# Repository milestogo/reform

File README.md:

#MNT keyboard remix
See keyboard-pcb for remix

# MNT Reform

This is the main repository for the MNT Reform open source laptop.

For details, check out [Finishing Reform](https://mntre.com/media/reform_md/2020-01-18-finishing-reform.html) and related articles.

## Impressions

## License

Copyright 2018-2020 MNT Research GmbH.

The following licenses are used in the project, unless specified differently in a particular subfolder:

- Schematics, PCBs: [CERN-OHL-S v2](https://www.ohwr.org/project/cernohl/wikis/uploads/002d0b7d5066e6b3829168730237bddb/cern_ohl_s_v2.txt)
- Other documentation, artwork, photos and drawings that are not trademarks (see below): [CC-BY-SA 4.0](https://creativecommons.org/licenses/by-sa/4.0/legalcode)
- Software, firmware: Various. [GPL 3.0](https://www.gnu.org/licenses/gpl-3.0.en.html) if not specified otherwise in the file/subdirectory.

The "MNT" and "MNT REFORM" logos are trademarks of MNT Research GmbH. You may not use these in derived works. The reason for this is that we cannot be responsible for regulatory issues with derived boards and we cannot support them. If someone sees an MNT brand on a product, it has to be clear that it comes from MNT Research and not from a third party.

## Made With

* [KiCAD EDA](http://kicad-pcb.org/)
* [OpenSCAD](https://www.openscad.org/)
* [LUFA](http://www.fourwalledcubicle.com/LUFA.php)
* Autodesk Fusion (Case parts)

## MNT Reform Team

* **Lukas F. Hartmann (mntmn)** - *Schematics, PCB*
* **Ana Dantas** - *Industrial Design*
* **Greta Melnik** - *Quality & Assembly, Sleeve*

## Credits and Contributions

* [fully automated technologies](https://fully.automated.ee/) - *inrush limiter circuit*

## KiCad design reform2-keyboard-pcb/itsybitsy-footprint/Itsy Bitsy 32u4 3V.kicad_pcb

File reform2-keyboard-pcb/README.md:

# keyboard remix by milestogo

This keyboard design is for educational purposes: for me to learn through experimenting, or for for you to educate me. 
Little remains of MNT's tested design. I have not tested. It may have dangerous or time-wasting errors. 

Changes from MNT reform
- Ergonomic key layout. 
- Removed backlight
- Added partial RGB backlighting. Keys ESC,~,1,2, F, Thumb keys, J, 9,0,-,= have backlights. This is enough to show battery voltage or where to put your hand in the dark. There are jumpers to bypass the top row LEDs, or add separate LED strips. This uses SK Mini-E rgb lights. Since they are bottom mount and optional, the power caps for them are also bottom & optional. 
- Added optional Kailh sockets for switches without RGB backlight. These sockets are cheaper than switches, so I like them in protototypes. there probably isn't thermal or short circuit clearance above the MNT motherboard, so use the direct direct solder holes.
- Removed surface mount Atmega32u4 and related voltage chips (cost and chip shortages). Instead it uses the 3 volt Adafruit itsy bitsy. https://learn.adafruit.com/introducting-itsy-bitsy-32u4/pinouts
you must hack a USB cable to connect the MCU  to the keyboard (see screenprint for "airwire"). 
- Optional power off switch/jumper that can completly remove power to the keyboard.
- Lots of break out pins, so that it should be possible to use the PCB with other MCUs.  
- Desktop option for through hole OLED modules. Available from online retailers

These changes are made available under the MIT License: 
Copyright © 2022 milestogo

Permission is hereby granted, free of charge, to any person obtaining a copy of this software and associated documentation files (the “Software”), to deal in the Software without restriction, including without limitation the rights to use, copy, modify, merge, publish, distribute, sublicense, and/or sell copies of the Software, and to permit persons to whom the Software is furnished to do so, subject to the following conditions:

The above copyright notice and this permission notice shall be included in all copies or substantial portions of the Software.

THE SOFTWARE IS PROVIDED “AS IS”, WITHOUT WARRANTY OF ANY KIND, EXPRESS OR IMPLIED, INCLUDING BUT NOT LIMITED TO THE WARRANTIES OF MERCHANTABILITY, FITNESS FOR A PARTICULAR PURPOSE AND NONINFRINGEMENT. IN NO EVENT SHALL THE AUTHORS OR COPYRIGHT HOLDERS BE LIABLE FOR ANY CLAIM, DAMAGES OR OTHER LIABILITY, WHETHER IN AN ACTION OF CONTRACT, TORT OR OTHERWISE, ARISING FROM, OUT OF OR IN CONNECTION WITH THE SOFTWARE OR THE USE OR OTHER DEALINGS IN THE SOFTWARE.

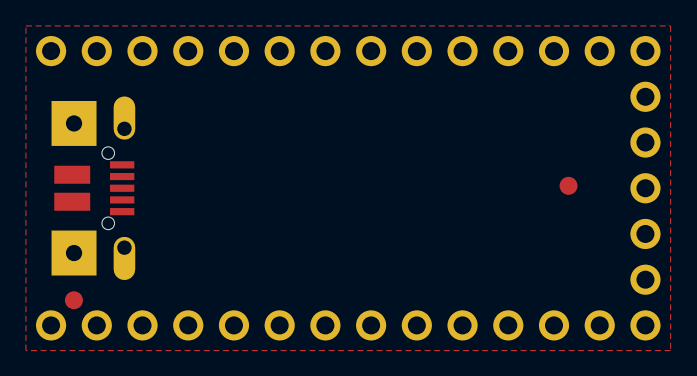
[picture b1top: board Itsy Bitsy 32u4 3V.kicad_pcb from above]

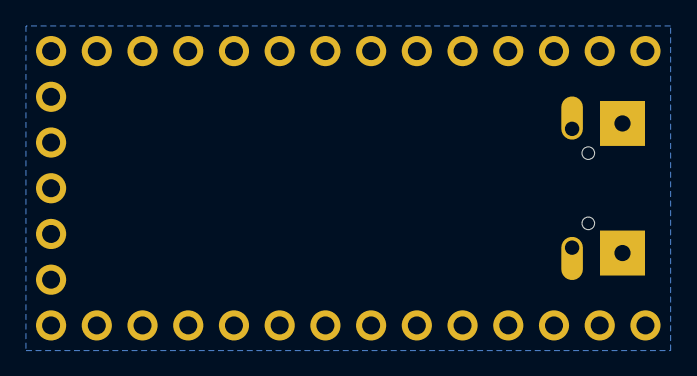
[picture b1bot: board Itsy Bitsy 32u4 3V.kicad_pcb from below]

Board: 2 copper layers, 9 parts (2 on the bottom side), 2 nets, no tracks yet.

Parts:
JP1: 1X05_ROUND
JP2, JP4: 1X14_ROUND70
U$2: PCBFEAT-REV-040
U$4: ADAFRUIT_5MM
U$7: ADAFRUIT_3.5MM
U$34, U$35: FIDUCIAL""; FIDUCIAL_1MM
X3: microUSB; 4UCONN_20329_V2

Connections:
GND: JP1.4, JP2.2, JP4.1, X3.BASE@1, X3.BASE@2, X3.GND, X3.SPRT@1, X3.SPRT@2, X3.SPRT@3, X3.SPRT@4
VBUS: JP2.3, X3.VBUS

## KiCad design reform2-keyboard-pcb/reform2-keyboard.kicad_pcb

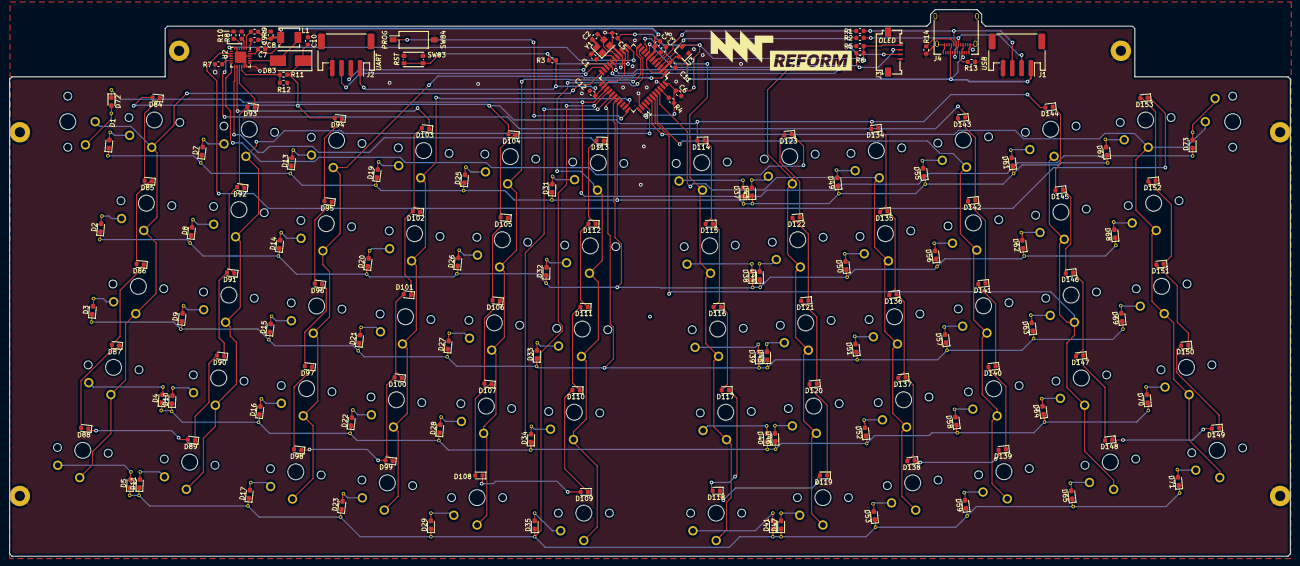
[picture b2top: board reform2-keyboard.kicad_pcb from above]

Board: 2 copper layers, 275.9 x 117.8 mm, 230 parts (1 on the bottom side), 168 nets.

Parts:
C1, C2: 18pF; C_0603_1608Metric
C3, C5, C8, C9, C11, C12: 1uF; C_0603_1608Metric
C4, C6: 0.1uF; C_0603_1608Metric
C7, C10: 4.7uF; C_0603_1608Metric
D1, D2, D3, D4, D5, D7, D8, D9, D10, D11, D13, D14, D15, D16, D17, D19, D20, D21, D22, D23, D25, D26, D27, D28, D29, D31, D32, D33, D34, D35, D37, D38, D39, D40, D41, D43, D44, D45, D46, D47, D49, D50, D51, D52, D53, D55, D56, D57, D58, D59, D61, D62, D63, D64, D65, D67, D68, D69, D70, D71, D72, D73: MMDL914T1G; D_0603_1608Metric_Pad1.05x0.95mm_HandSolderPlusVias
D83: B250-13-F; D_SMB_Handsoldering
D84, D85, D86, D87, D88, D89, D90, D91, D92, D93, D94, D95, D96, D97, D98, D99, D100, D101, D102, D103, D104, D105, D106, D107, D108, D109, D110, D111, D112, D113, D114, D115, D116, D117, D118, D119, D120, D121, D122, D123, D134, D135, D136, D137, D138, D139, D140, D141, D142, D143, D144, D145, D146, D147, D148, D149, D150, D151, D152, D153: WLED; LED_0603_1608Metric
GFX1, GFX2: MNT; mntreform
H1: MH1; MountingHole_2.2mm_M2_Pad
H2: MH2; MountingHole_2.2mm_M2_Pad
H3: MH3; MountingHole_2.2mm_M2_Pad
H4: MH4; MountingHole_2.2mm_M2_Pad
H5: MH5; MountingHole_2.2mm_M2_Pad
H6: MH6; MountingHole_2.2mm_M2_Pad
J1: USB; JST_PH_S4B-PH-SM4-TB_1x04-1MP_P2.00mm_Horizontal
J2: UART; JST_PH_S4B-PH-SM4-TB_1x04-1MP_P2.00mm_Horizontal
J3: AUX; Molex_200528-0040_1x04-1MP_P1.00mm_Horizontal
J4: USB_C_Receptacle_USB2.0; USB_C_Receptacle_Amphenol_12401610E4-2A
L1: 10uH; IND_SRP4020TA-150M
R1, R2: 22; R_0603_1608Metric
R3: 10k; R_0603_1608Metric
R4, R9: 0; R_0603_1608Metric
R5, R6: 4.7k; R_0603_1608Metric
R7: 62K; R_0603_1608Metric
R8: 604K; R_0603_1608Metric
R10: 715K; R_0603_1608Metric
R11: 1M; R_0603_1608Metric
R12: 54.9K; R_0603_1608Metric
R13, R14: 5.1k; R_0603_1608Metric
SW1, SW2, SW3, SW4, SW5, SW7, SW8, SW9, SW10, SW11, SW13, SW14, SW15, SW16, SW17, SW19, SW20, SW21, SW22, SW23, SW25, SW26, SW27, SW28, SW29, SW31, SW32, SW33, SW34, SW35, SW37, SW38, SW39, SW40, SW41, SW43, SW44, SW45, SW46, SW47, SW49, SW50, SW51, SW52, SW53, SW55, SW56, SW57, SW58, SW59, SW61, SW62, SW63, SW64, SW65, SW67, SW68, SW69, SW70, SW71, SW72, SW73: Choc; PG1350
SW83: RESET; SW_Push_1P1T_NO_CK_KMR2
SW84: SW_DIP_x01; SW_DIP_SPSTx01_Slide_Omron_A6S-110x_W8.9mm_P2.54mm
U1: ATMEGA32U4-AU; TQFP-44_10x10mm_Pitch0.8mm
U2: TPS61185; VQFN-24-1EP_4x4mm_P0.5mm_EP2.45x2.45mm
U3: MCP1700-3302E_SOT23; SOT-23
Y1: 16MHz; Crystal_SMD_3225-4Pin_3.2x2.5mm

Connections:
+3V3: C5.1, C6.1, C12.1, J2.1, J3.1, R3.1, R4.2, R5.1, R6.1, U1.14, U1.24, U1.34, U1.44, U3.2
+5V: C4.1, C7.1, C8.1, C11.1, J1.1, J4.A4, J4.A9, J4.B4, J4.B9, L1.1, R9.1, U1.2, U1.7, U2.23, U3.3
/Reform KBD MCU/UD+: R1.1, U1.4
/Reform KBD MCU/UD-: R2.1, U1.3
COL1: SW1.1, SW2.1, SW3.1, SW4.1, SW5.1, SW72.1, U1.22
COL2: SW7.1, SW8.1, SW9.1, SW10.1, SW11.1, U1.36
COL3: SW13.1, SW14.1, SW15.1, SW16.1, SW17.1, U1.1
COL4: SW19.1, SW20.1, SW21.1, SW22.1, SW23.1, U1.32
COL5: SW25.1, SW26.1, SW27.1, SW28.1, SW29.1, U1.11
COL6: SW31.1, SW32.1, SW33.1, SW34.1, SW35.1, U1.10
COL7: SW37.1, SW38.1, SW39.1, SW40.1, SW41.1, U1.9
COL8: SW43.1, SW44.1, SW45.1, SW46.1, SW47.1, U1.8
COL9: SW49.1, SW50.1, SW51.1, SW52.1, SW53.1, U1.41
COL10: SW55.1, SW56.1, SW57.1, SW58.1, SW59.1, U1.40
COL11: SW61.1, SW62.1, SW63.1, SW64.1, SW65.1, U1.39
COL12: SW67.1, SW68.1, SW69.1, SW70.1, SW71.1, SW73.1, U1.38
D+: J1.3, J4.A6, J4.B6, R1.2
D-: J1.2, J4.A7, J4.B7, R2.2
DISP_SCL: J3.2, R6.2, U1.18
DISP_SDA: J3.3, R5.2, U1.19
GND: C1.2, C2.2, C3.2, C4.2, C5.2, C6.2, C7.2, C8.2, C9.2, C10.2, C11.2, C12.2, H1.1, H2.1, H3.1, H4.1, H5.1, H6.1, J1.4, J2.4, J3.4, J4.A1, J4.A12, J4.B1, J4.B12, J4.S1, R7.2, R8.2, R10.2, R12.2, R13.1, R14.2, SW83.2, SW84.2, U1.5, U1.15, U1.23, U1.35, U1.43, U2.5, U2.17, U2.18, U2.22, U2.25, U3.1, Y1.2, Y1.4
unnamed: C1.1, U1.17, Y1.1
unnamed: C2.1, U1.16, Y1.3
unnamed: C3.1, U1.6
unnamed: C9.1, U2.24
unnamed: C10.1, D83.1, D84.2, D94.2, D104.2, D114.2, D134.2, D144.2, R11.1
unnamed: D1.2, SW1.2
unnamed: D2.2, SW2.2
unnamed: D3.2, SW3.2
unnamed: D4.2, SW4.2
unnamed: D5.2, SW5.2
unnamed: D7.2, SW7.2
unnamed: D8.2, SW8.2
unnamed: D9.2, SW9.2
unnamed: D10.2, SW10.2
unnamed: D11.2, SW11.2
unnamed: D13.2, SW13.2
unnamed: D14.2, SW14.2
unnamed: D15.2, SW15.2
unnamed: D16.2, SW16.2
unnamed: D17.2, SW17.2
unnamed: D19.2, SW19.2
unnamed: D20.2, SW20.2
unnamed: D21.2, SW21.2
unnamed: D22.2, SW22.2
unnamed: D23.2, SW23.2
unnamed: D25.2, SW25.2
unnamed: D26.2, SW26.2
unnamed: D27.2, SW27.2
unnamed: D28.2, SW28.2
unnamed: D29.2, SW29.2
unnamed: D31.2, SW31.2
unnamed: D32.2, SW32.2
unnamed: D33.2, SW33.2
unnamed: D34.2, SW34.2
unnamed: D35.2, SW35.2
unnamed: D37.2, SW37.2
unnamed: D38.2, SW38.2
unnamed: D39.2, SW39.2
unnamed: D40.2, SW40.2
unnamed: D41.2, SW41.2
unnamed: D43.2, SW43.2
unnamed: D44.2, SW44.2
unnamed: D45.2, SW45.2
unnamed: D46.2, SW46.2
unnamed: D47.2, SW47.2
unnamed: D49.2, SW49.2
unnamed: D50.2, SW50.2
unnamed: D51.2, SW51.2
unnamed: D52.2, SW52.2
unnamed: D53.2, SW53.2
unnamed: D55.2, SW55.2
unnamed: D56.2, SW56.2
unnamed: D57.2, SW57.2
unnamed: D58.2, SW58.2
unnamed: D59.2, SW59.2
unnamed: D61.2, SW61.2
unnamed: D62.2, SW62.2
unnamed: D63.2, SW63.2
unnamed: D64.2, SW64.2
unnamed: D65.2, SW65.2
unnamed: D67.2, SW67.2
unnamed: D68.2, SW68.2
unnamed: D69.2, SW69.2
unnamed: D70.2, SW70.2
unnamed: D71.2, SW71.2
unnamed: D72.2, SW72.2
unnamed: D73.2, SW73.2
unnamed: D83.2, L1.2, U2.19, U2.20
unnamed: D84.1, D85.2
unnamed: D85.1, D86.2
unnamed: D86.1, D87.2
unnamed: D87.1, D88.2
unnamed: D88.1, D89.2
unnamed: D89.1, D90.2
unnamed: D90.1, D91.2
unnamed: D91.1, D92.2
unnamed: D92.1, D93.2
unnamed: D93.1, U2.15
unnamed: D94.1, D95.2
unnamed: D95.1, D96.2
unnamed: D96.1, D97.2
unnamed: D97.1, D98.2
unnamed: D98.1, D99.2
unnamed: D100.1, D101.2
unnamed: D99.1, D100.2
unnamed: D101.1, D102.2
unnamed: D102.1, D103.2
unnamed: D103.1, U2.14
unnamed: D104.1, D105.2
unnamed: D105.1, D106.2
unnamed: D106.1, D107.2
unnamed: D107.1, D108.2
unnamed: D108.1, D109.2
unnamed: D109.1, D110.2
unnamed: D110.1, D111.2
unnamed: D111.1, D112.2
unnamed: D112.1, D113.2
unnamed: D113.1, U2.13
unnamed: D114.1, D115.2
unnamed: D115.1, D116.2
unnamed: D116.1, D117.2
unnamed: D117.1, D118.2
unnamed: D118.1, D119.2
unnamed: D119.1, D120.2
unnamed: D120.1, D121.2
unnamed: D121.1, D122.2
unnamed: D122.1, D123.2
unnamed: D123.1, U2.12
unnamed: D134.1, D135.2
unnamed: D135.1, D136.2
unnamed: D136.1, D137.2
unnamed: D137.1, D138.2
unnamed: D138.1, D139.2
unnamed: D139.1, D140.2
unnamed: D140.1, D141.2
unnamed: D141.1, D142.2
unnamed: D142.1, D143.2
unnamed: D143.1, U2.9
unnamed: D144.1, D145.2
unnamed: D145.1, D146.2
unnamed: D146.1, D147.2
unnamed: D147.1, D148.2
unnamed: D148.1, D149.2
unnamed: D149.1, D150.2
unnamed: D150.1, D151.2
unnamed: D151.1, D152.2
unnamed: D152.1, D153.2
unnamed: D153.1, U2.8
unnamed: J4.A5, R13.2
unnamed: J4.B5, R14.1
unnamed: R4.1, U1.42
unnamed: R7.1, U2.11
unnamed: R8.1, U2.2
unnamed: R9.2, U2.1
unnamed: R10.1, U2.3
unnamed: R11.2, R12.1, U2.16
PROG: SW84.1, U1.33
PWM: U1.12, U2.6
RESET: R3.2, SW83.1, U1.13
ROW1: D1.1, D7.1, D13.1, D19.1, D25.1, D31.1, D37.1, D43.1, D49.1, D55.1, D61.1, D67.1, U1.30
ROW2: D2.1, D8.1, D14.1, D20.1, D26.1, D32.1, D38.1, D44.1, D50.1, D56.1, D62.1, D68.1, U1.29
ROW3: D3.1, D9.1, D15.1, D21.1, D27.1, D33.1, D39.1, D45.1, D51.1, D57.1, D63.1, D69.1, U1.28
ROW4: D4.1, D10.1, D16.1, D22.1, D28.1, D34.1, D40.1, D46.1, D52.1, D58.1, D64.1, D70.1, U1.27
ROW5: D5.1, D11.1, D17.1, D23.1, D29.1, D35.1, D41.1, D47.1, D53.1, D59.1, D65.1, D71.1, U1.26
ROW6: D72.1, D73.1, U1.25
UART_RX: J2.2, U1.20
UART_TX: J2.3, U1.21

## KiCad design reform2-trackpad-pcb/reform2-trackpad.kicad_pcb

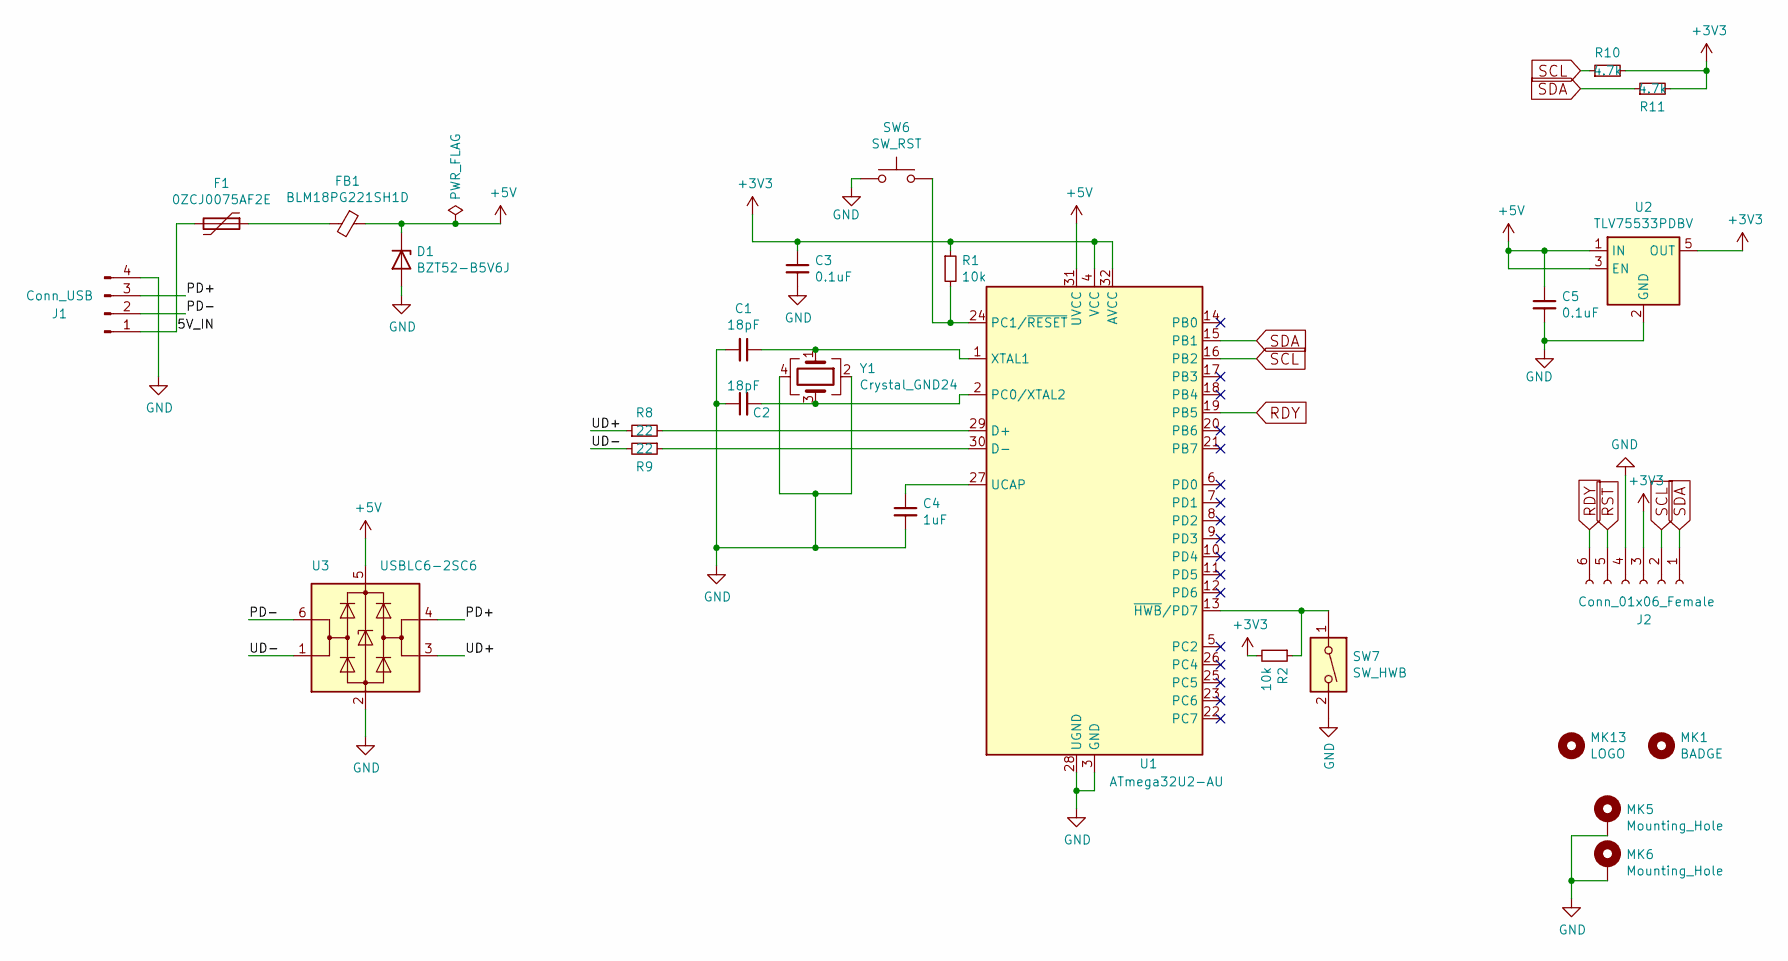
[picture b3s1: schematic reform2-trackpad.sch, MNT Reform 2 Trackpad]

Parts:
C1, C2: 18pF; C_0603_1608Metric
C3, C5: 0.1uF; C_0603_1608Metric
C4: 1uF; C_0603_1608Metric
D1: BZT52-B5V6J; D_SOD-123
F1: 0ZCJ0075AF2E; Fuse_1206_3216Metric_Castellated
FB1: BLM18PG221SH1D; L_0603_1608Metric
J1: Conn_USB; JST_PH_B4B-PH-K_1x04_P2.00mm_Vertical
J2: Conn_01x06_Female; Hirose_FH12-6S-0.5SH_1x06-1MP_P0.50mm_Horizontal
MK1: BADGE; reform2-trackpadctrl-badge
MK5, MK6: Mounting_Hole; MountingHole_2.2mm_M2_Pad
MK13: LOGO; mnt-minilogo
R1, R2: 10k; R_0603_1608Metric
R8, R9: 22; R_0603_1608Metric
R10, R11: 4.7k; R_0603_1608Metric
SW6: SW_RST; SW_Push_1P1T_NO_CK_KMR2
SW7: SW_HWB; SW_DIP_SPSTx01_Slide_Omron_A6S-110x_W8.9mm_P2.54mm
U1: ATmega32U2-AU; TQFP-32_7x7mm_P0.8mm
U2: TLV75533PDBV; SOT-23-5
U3: USBLC6-2SC6; SOT-23-6
Y1: Crystal_GND24; Crystal_SMD_3225-4Pin_3.2x2.5mm

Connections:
+3V3: C3.1, J2.3, R1.1, R2.2, R10.2, R11.2, U1.4 (VCC), U1.32 (AVCC), U2.5 (OUT)
+5V: C5.1, D1.1 (K), FB1.1, U1.31 (UVCC), U2.1 (IN), U2.3 (EN), U3.5 (VBUS)
/5V_IN: F1.2, J1.1
/PD+: J1.3, U3.4 (I/O2)
/PD-: J1.2, U3.6 (I/O1)
/UD+: R8.1, U3.3 (I/O2)
/UD-: R9.2, U3.1 (I/O1)
GND: C1.2, C2.1, C3.2, C4.2, C5.2, D1.2 (A), J1.4, J2.4, MK5.1, MK6.1, SW6.1, SW7.2, U1.3 (GND), U1.28 (UGND), U2.2 (GND), U3.2 (GND), Y1.2, Y1.4
unnamed: C1.1, U1.1 (XTAL1), Y1.1
unnamed: C2.2, U1.2 (PC0/XTAL2), Y1.3
unnamed: C4.1, U1.27 (UCAP)
unnamed: F1.1, FB1.2
unnamed: R1.2, SW6.2, U1.24 (PC1/~RESET)
unnamed: R2.1, SW7.1, U1.13 (~HWB~/PD7)
unnamed: R8.2, U1.29 (D+)
unnamed: R9.1, U1.30 (D-)
RDY: J2.6, U1.19 (PB5)
RST: J2.5
SCL: J2.2, R10.1, U1.16 (PB2)
SDA: J2.1, R11.1, U1.15 (PB1)

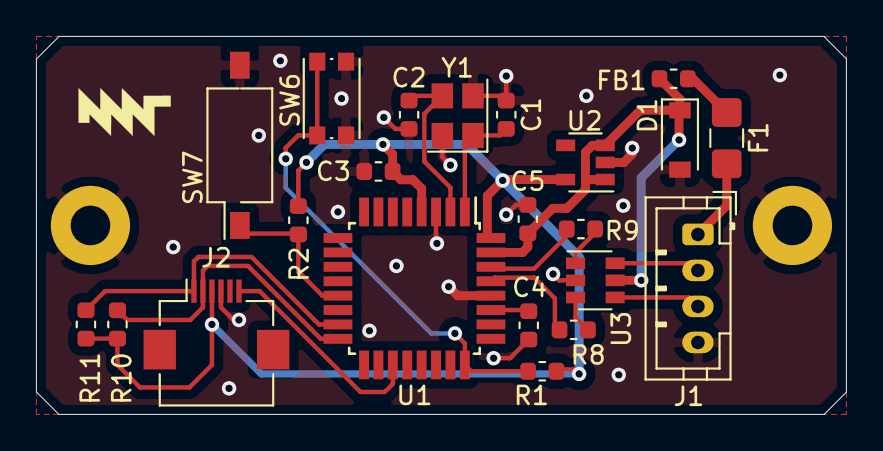
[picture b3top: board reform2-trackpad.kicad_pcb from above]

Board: 2 copper layers, 45.0 x 21.0 mm, 26 parts (1 on the bottom side), 19 nets.

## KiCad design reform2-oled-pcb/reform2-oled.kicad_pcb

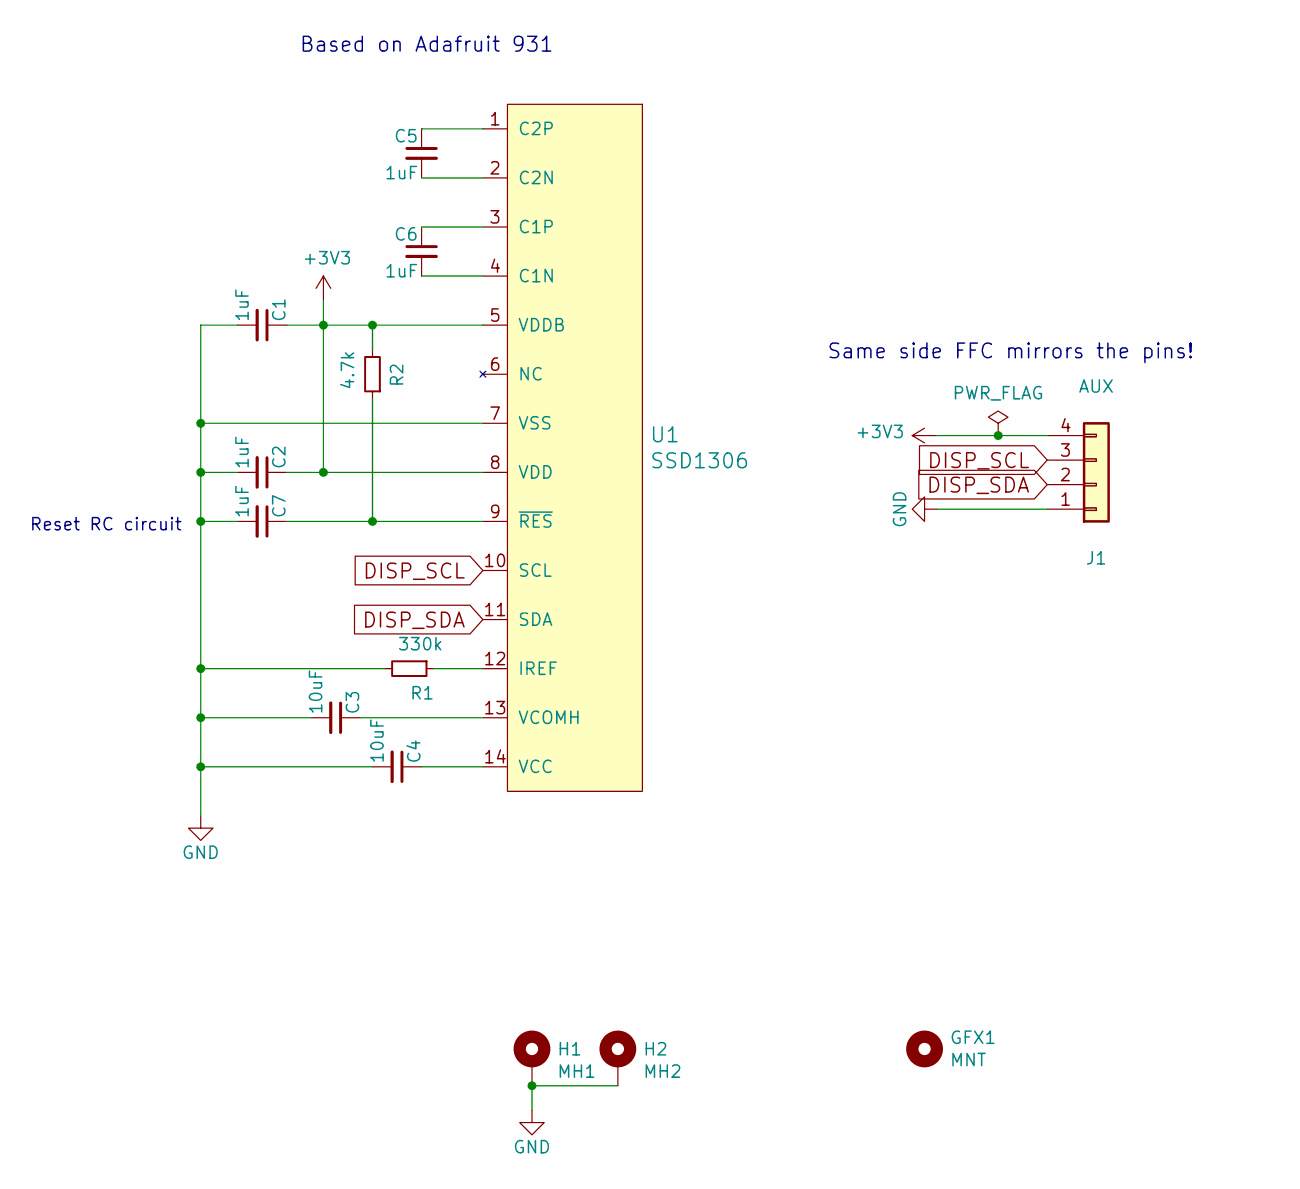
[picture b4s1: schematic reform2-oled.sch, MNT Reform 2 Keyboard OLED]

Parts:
C1, C2, C5, C6, C7: 1uF; C_0603_1608Metric_Pad1.05x0.95mm_HandSolder
C3, C4: 10uF; C_0603_1608Metric_Pad1.05x0.95mm_HandSolder
GFX1: MNT; mntreform
H1: MH1; MountingHole_2.2mm_M2_Pad
H2: MH2; MountingHole_2.2mm_M2_Pad
J1: AUX; Molex_200528-0040_1x04-1MP_P1.00mm_Horizontal
R1: 330k; R_0603_1608Metric_Pad1.05x0.95mm_HandSolder
R2: 4.7k; R_0603_1608Metric_Pad1.05x0.95mm_HandSolder
U1: SSD1306; SSD1306_OLED-0.91-128x32

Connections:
+3V3: C1.1, C2.1, J1.4, R2.2, U1.5 (VDDB), U1.8 (VDD)
DISP_SCL: J1.3, U1.10 (SCL)
DISP_SDA: J1.2, U1.11 (SDA)
GND: C1.2, C2.2, C3.2, C4.2, C7.2, H1.1, H2.1, J1.1, R1.2, U1.7 (VSS)
unnamed: C3.1, U1.13 (VCOMH)
unnamed: C4.1, U1.14 (VCC)
unnamed: C5.1, U1.1 (C2P)
unnamed: C5.2, U1.2 (C2N)
unnamed: C6.1, U1.3 (C1P)
unnamed: C6.2, U1.4 (C1N)
unnamed: C7.1, R2.1, U1.9 (~RES)
unnamed: R1.1, U1.12 (IREF)

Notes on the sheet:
Based on Adafruit 931
Reset RC circuit
Same side FFC mirrors the pins!

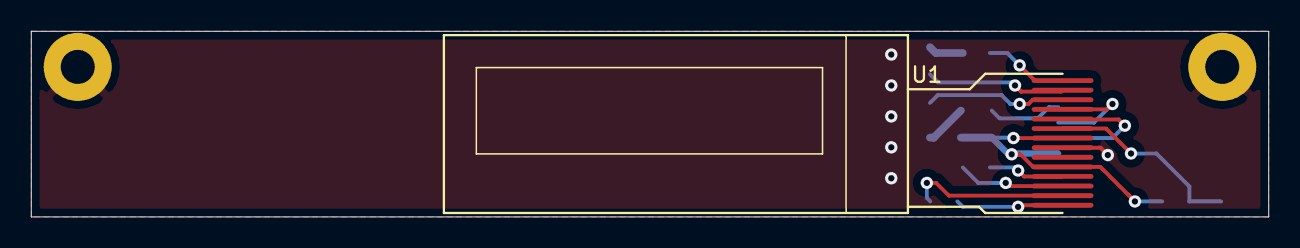
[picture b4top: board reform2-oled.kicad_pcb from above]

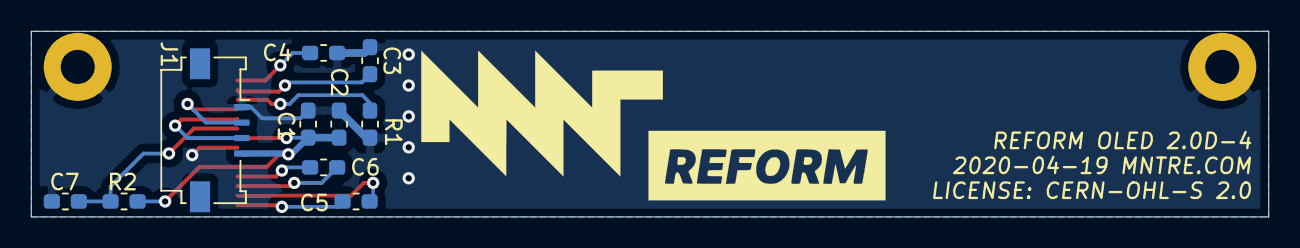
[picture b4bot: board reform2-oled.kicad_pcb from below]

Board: 2 copper layers, 80.0 x 12.0 mm, 14 parts (11 on the bottom side), 12 nets.

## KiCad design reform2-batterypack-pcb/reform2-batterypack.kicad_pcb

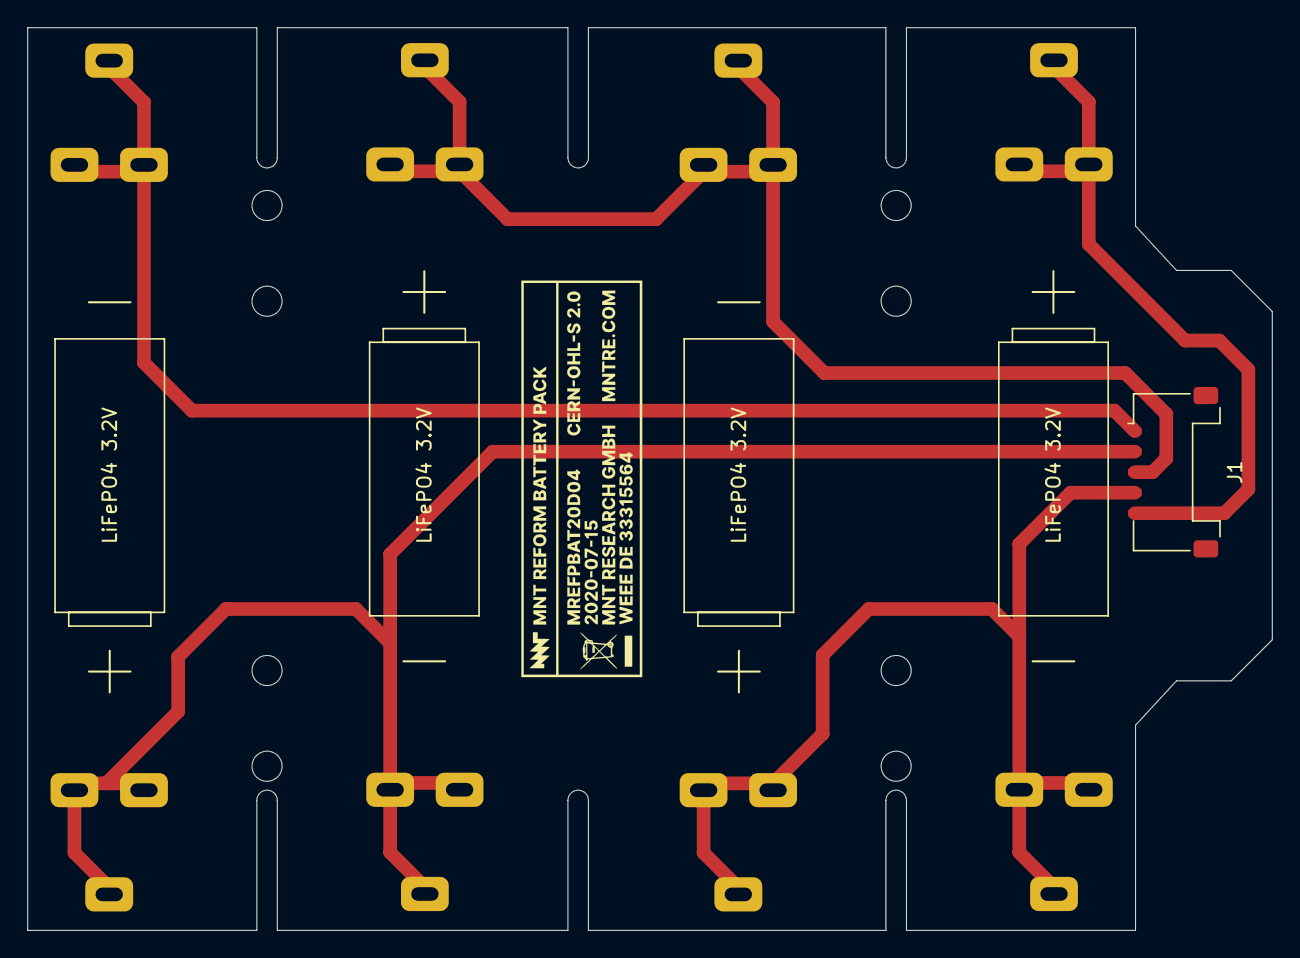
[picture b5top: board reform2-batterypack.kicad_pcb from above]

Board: 2 copper layers, 91.0 x 66.0 mm, 13 parts (0 on the bottom side), 5 nets.

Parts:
H1, H2, H3, H4, H5, H6, H7, H8: MountingHole; MountingHole_2.2mm_M2
J1: Conn_01x05_Female; Molex_Pico-Lock_504050-0591_1x05-1MP_P1.50mm_Horizontal
U1, U2, U3, U4: KEYSTONE_54; Keystone54

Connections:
unnamed: J1.1, U1.4, U1.5, U1.6
unnamed: J1.2, U1.1, U1.2, U1.3, U2.4, U2.5, U2.6
unnamed: J1.3, U2.1, U2.2, U2.3, U3.4, U3.5, U3.6
unnamed: J1.4, U3.1, U3.2, U3.3, U4.4, U4.5, U4.6
unnamed: J1.5, U4.1, U4.2, U4.3

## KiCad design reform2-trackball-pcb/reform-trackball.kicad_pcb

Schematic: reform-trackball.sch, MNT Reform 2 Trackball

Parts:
C1, C2: 18pF; C_0603_1608Metric
C3, C5: 0.1uF; C_0603_1608Metric
C4: 1uF; C_0603_1608Metric
D1, D2, D3, D4, D5: LED_Small; LED_0603_1608Metric
J1: Conn_USB; JST_PH_B4B-PH-K_1x04_P2.00mm_Vertical
J2: Conn_01x06_Female; Hirose_FH12-6S-0.5SH_1x06-1MP_P0.50mm_Horizontal
MK5, MK6, MK7, MK8, MK9, MK10, MK11, MK12: Mounting_Hole; MountingHole_2.2mm_M2_Pad
MK13: LOGO; mntreform
R1, R2: 10k; R_0603_1608Metric
R3, R4, R5, R6, R7: 475; R_0603_1608Metric
R8, R9: 22; R_0603_1608Metric
R10, R11: 4.7k; R_0603_1608Metric
SW1, SW2, SW3, SW4, SW5: Choc; PG1350
SW6: SW_RST; SW_Push_1P1T_NO_CK_KMR2
SW7: SW_HWB; SW_DIP_SPSTx01_Slide_Omron_A6S-110x_W8.9mm_P2.54mm
U1: ATmega32U2-AU; TQFP-32_7x7mm_Pitch0.8mm
U2: TLV75533PDBV; SOT-23-5
Y1: Crystal_GND24; Crystal_SMD_3225-4pin_3.2x2.5mm_HandSoldering

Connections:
+3V3: C3.1, J2.6, R1.1, R2.2, R3.2, R4.2, R5.2, R6.2, R7.2, R10.2, R11.2, U1.4 (VCC), U1.32 (AVCC), U2.5
+5V: C5.1, J1.1, U1.31 (UVCC), U2.1, U2.3
GND: C1.2, C2.1, C3.2, C4.2, C5.2, J1.4, J2.1, MK5.1, MK6.1, MK7.1, MK8.1, MK9.1, MK10.1, MK11.1, MK12.1, SW1.2, SW2.2, SW3.2, SW4.2, SW5.2, SW6.1, SW7.2, U1.3 (GND), U1.28 (UGND), U2.2, Y1.2, Y1.4
MT: J2.2, U1.19 (PB5)
unnamed: C1.1, U1.1 (XTAL1), Y1.1
unnamed: C2.2, U1.2 (PC0/XTAL2), Y1.3
unnamed: C4.1, U1.27 (UCAP)
unnamed: D1.1 (K), U1.22 (PC7)
unnamed: D1.2 (A), R3.1
unnamed: D2.1 (K), U1.23 (PC6)
unnamed: D2.2 (A), R4.1
unnamed: D3.1 (K), U1.25 (PC5)
unnamed: D3.2 (A), R5.1
unnamed: D4.1 (K), U1.26 (PC4)
unnamed: D4.2 (A), R6.1
unnamed: D5.1 (K), U1.5 (PC2)
unnamed: D5.2 (A), R7.1
unnamed: J1.2, R9.2
unnamed: J1.3, R8.1
unnamed: R1.2, SW6.2, U1.24 (PC1/~RESET)
unnamed: R2.1, SW7.1, U1.13 (~HWB~/PD7)
unnamed: R8.2, U1.29 (D+)
unnamed: R9.1, U1.30 (D-)
unnamed: SW1.1, U1.10 (PD4)
unnamed: SW2.1, U1.9 (PD3)
unnamed: SW3.1, U1.8 (PD2)
unnamed: SW4.1, U1.7 (PD1)
unnamed: SW5.1, U1.6 (PD0)
SCL: J2.4, R10.1, U1.16 (PB2)
SDA: J2.3, R11.1, U1.15 (PB1)

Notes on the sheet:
Attention! This pinout is mirrored in respect to the trackball sensor for mechanical alignment!

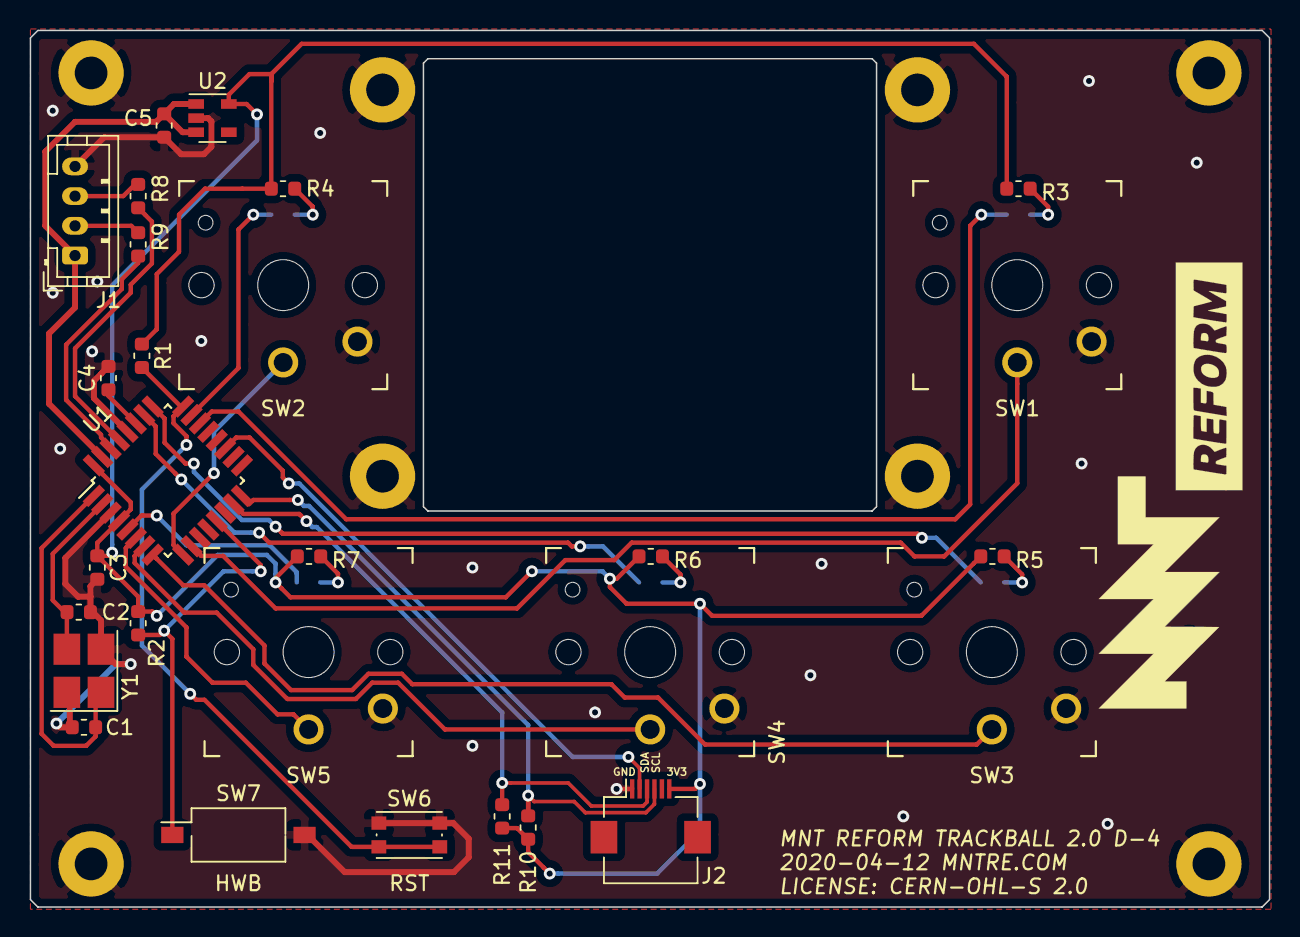
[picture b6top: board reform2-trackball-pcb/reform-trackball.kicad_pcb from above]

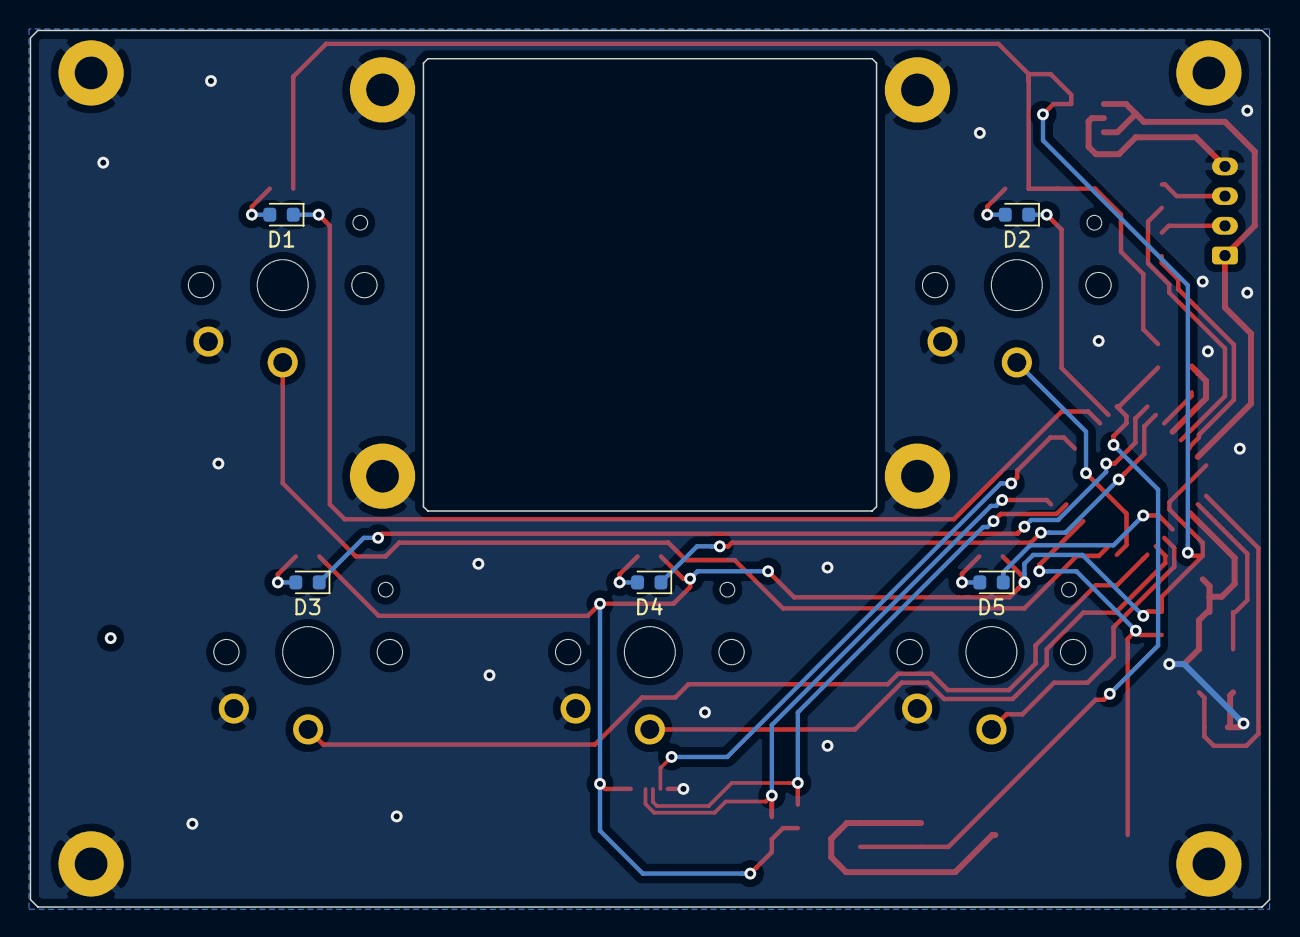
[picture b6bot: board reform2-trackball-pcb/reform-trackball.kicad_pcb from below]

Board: 2 copper layers, 83.4 x 59.0 mm, 42 parts (10 on the bottom side), 30 nets.

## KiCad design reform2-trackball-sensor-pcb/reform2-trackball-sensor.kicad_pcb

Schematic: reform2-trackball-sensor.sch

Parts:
C1: 1uF; C_0603_1608Metric
C2: 0.1uF; C_0603_1608Metric
C3: 10uF; C_0603_1608Metric
H1, H2, H3, H4, H5, H6: MountingHole; MountingHole_2.2mm_M2
H7, H8: LOGO; mnt-minilogo
J1: Conn_01x06_Male; Hirose_FH12-6S-0.5SH_1x06-1MP_P0.50mm_Horizontal
R1: 0; R_0603_1608Metric
U1: PAT9125EL

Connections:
+3V3: C1.1, C2.1, J1.1, U1.1 (VLD), U1.3 (Vdd)
/MOTION: J1.5, U1.7 (MOTION)
/SCL: J1.3, U1.5 (SCL)
/SDA: J1.4, U1.6 (SDA)
GND: C1.2, C2.2, C3.2, J1.6, R1.1, U1.4 (GND)
unnamed: C3.1, U1.2 (VDDA)
unnamed: R1.2, U1.8 (ID_SEL)

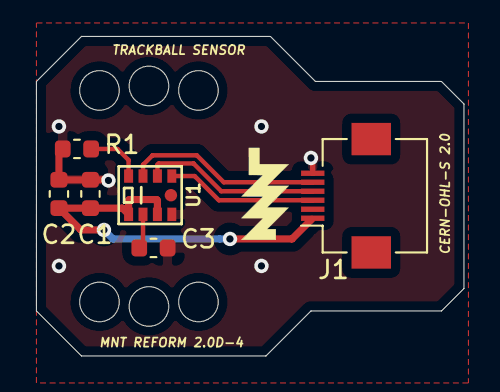
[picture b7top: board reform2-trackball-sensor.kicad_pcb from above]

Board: 2 copper layers, 23.8 x 17.8 mm, 14 parts (1 on the bottom side), 7 nets.

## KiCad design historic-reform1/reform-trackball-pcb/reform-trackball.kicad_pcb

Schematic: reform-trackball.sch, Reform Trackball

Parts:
C1, C2: 18pF; C_0603_HandSoldering
C3: 0.1uF; C_0603_HandSoldering
C4: 1uF; C_0603_HandSoldering
J1: Conn_USB; Pin_Header_Straight_1x04_Pitch2.00mm
J2: Conn_Sensor; Pin_Header_Straight_1x08_Pitch2.54mm
J3: Conn_RST; Pin_Header_Straight_1x02_Pitch2.54mm
J6: Conn_PWR; Pin_Header_Straight_1x02_Pitch2.54mm
J7: Conn_HWB; Pin_Header_Straight_1x02_Pitch2.54mm
MK2, MK3, MK4: Mounting_Hole; MountingHole_2.2mm_M2_DIN965
MK5, MK6, MK7, MK8: Mounting_Hole; MountingHole_4mm
MK9, MK10, MK11, MK12: Mounting_Hole; MountingHole_3.2mm_M3_DIN965
MK13: LOGO; mnt
MK14: LOGO2; reform04
R1, R2: 10k; R_0603_HandSoldering
SW1, SW2: ML; cherry-ml
U1: ATmega32U2-AU; TQFP-32_7x7mm_Pitch0.8mm
Y1: Crystal_GND24; Crystal_SMD_3225-4pin_3.2x2.5mm_HandSoldering

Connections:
+5V: C3.1, J1.4, J2.1, J6.2, R1.1, R2.1, U1.4 (VCC), U1.31 (UVCC), U1.32 (AVCC)
GND: C1.2, C2.1, C3.2, C4.2, J1.1, J2.7, J3.1, J6.1, J7.1, SW1.4, SW2.4, U1.3 (GND), U1.28 (UGND), Y1.2, Y1.4
MISO: J2.2, U1.17 (PB3)
MOSI: J2.3, U1.16 (PB2)
MT: J2.6, U1.19 (PB5)
unnamed: C1.1, U1.1 (XTAL1), Y1.1
unnamed: C2.2, U1.2 (PC0/XTAL2), Y1.3
unnamed: C4.1, U1.27 (UCAP)
unnamed: J1.2, U1.29 (D+)
unnamed: J1.3, U1.30 (D-)
unnamed: J3.2, R1.2, U1.24 (PC1/~RESET)
unnamed: J7.2, R2.2, U1.13 (~HWB~/PD7)
unnamed: SW1.2, U1.7 (PD1)
unnamed: SW2.2, U1.6 (PD0)
RESET: J2.8, U1.20 (PB6)
SCLK: J2.4, U1.15 (PB1)
SS: J2.5, U1.21 (PB7)

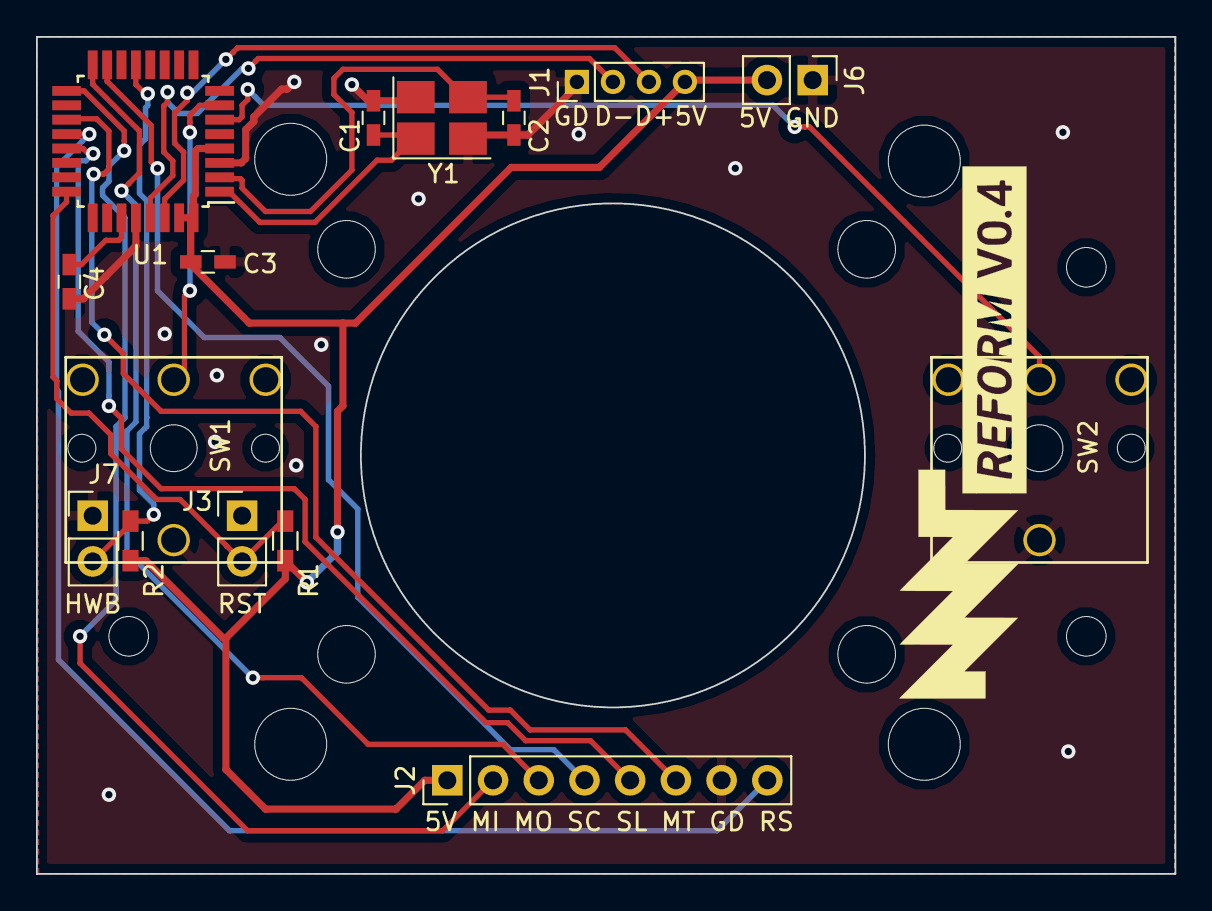
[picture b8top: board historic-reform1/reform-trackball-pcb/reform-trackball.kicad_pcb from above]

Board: 2 copper layers, 63.2 x 46.5 mm, 28 parts (0 on the bottom side), 17 nets.

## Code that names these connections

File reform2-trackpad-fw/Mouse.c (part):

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// Registers
#define Product_ID  0x00
#define Revision_ID 0x01
#define Motion  0x02
#define Delta_X_L 0x03
#define Delta_X_H 0x04
#define Delta_Y_L 0x05
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			},
	};

// LM PD0 input pullup
// RM PD1 input pullup

#define ADDR_SENSOR (0x74<<1)

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  MouseReport->Y = 0;

  // sensor ready?
  uint8_t rdy = PINB&(1<<5);
  if (!rdy) {
    if (report_lift) {
      // we still have to end a short click event
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

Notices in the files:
reform2-trackpad-fw/Mouse.c:
Copyright (C) Dean Camera, 2018.
Copyright 2018  Dean Camera (dean [at] fourwalledcubicle [dot] com)
historic-reform1/reform-trackball-pcb/reform-trackball.sch:
License: GPLv3+ https://www.gnu.org/licenses/gpl-3.0.en.html
Copyright 2017,2018 Lukas F. Hartmann / mntmn
reform2-oled-pcb/reform2-oled.kicad_pcb:
LICENSE: CERN-OHL-S 2.0
reform2-trackball-pcb/reform-trackball.sch:
Copyright 2017-2020 MNT Research GmbH
reform2-trackball-sensor-pcb/reform2-trackball-sensor.kicad_pcb:
CERN-OHL-S 2.0
